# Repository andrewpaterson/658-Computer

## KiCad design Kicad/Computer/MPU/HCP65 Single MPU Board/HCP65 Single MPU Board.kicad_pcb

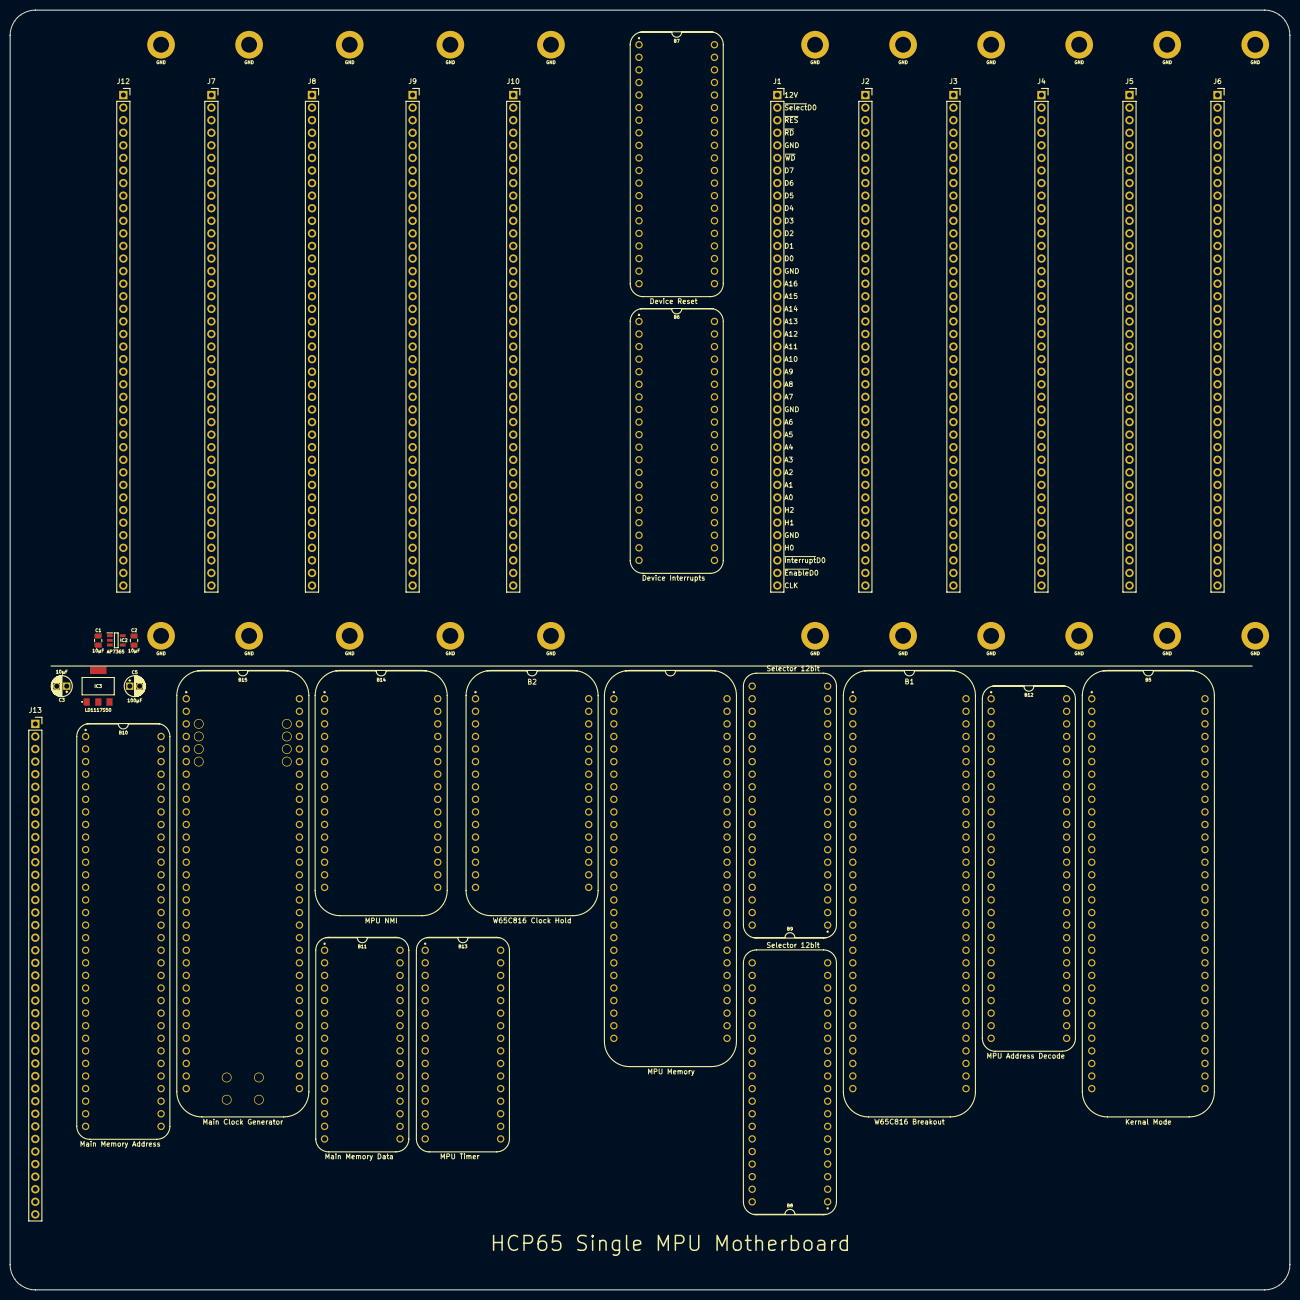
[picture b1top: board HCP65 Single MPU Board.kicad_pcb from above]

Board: 2 copper layers, 258.4 x 258.4 mm, 54 parts (0 on the bottom side), 186 nets, no tracks yet.

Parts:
B1: W65C816 Breakout; HCP65_W65C816_Breakout
B2: W65C816 Clock Hold; HCP65_W65C816_Clock_Hold
B4: MPU Memory; HCP65_MPU_Memory
B5: Kernal Mode; HCP65_Kernal_Mode
B6: Device Interrupts; HCP65_Device_Interrupts
B7: Device Reset; HCP65_Device_Reset
B8, B9: Selector 12bit; HCP65_Selector_12bit
B10: Main Memory Address; HCP65_Main_Memory_Address
B11: Main Memory Data; HCP65_Main_Memory_Data
B12: MPU Address Decode; HCP65_MPU_Address_Decode
B13: MPU Timer; HCP65_MPU_Timer
B14: MPU NMI; HCP65_MPU_NMI
B15: Main Clock Generator; HCP65_Clock_Generator
C1, C2: 10µF; C_0805
C3: 10μF; CP_Radial_D4.0mm_P2.00mm
C5: 100μF; CP_Radial_D4.0mm_P2.00mm
H3, H4, H5, H6, H7, H8, H9, H10, H11, H12, H13, H14, H15, H16, H17, H18, H19, H20, H21, H22, H23, H24: MountingHole_Pad; HCP65_MountingHole_M3_
IC2: AP7365-33WG-7; SOT95P285X130-5N
IC3: LD1117S50C; LD1117S33C
J1, J2, J3, J4, J5, J6, J7, J8, J9, J10, J12, J13: Conn_01x40_Socket; PinSocket_1x40_P2.54mm_Vertical

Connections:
/3.3V: B1.20 (BE), B1.21 (RDY), B1.44 (~ABORT), B2.4 (~Hold_High), B2.16 (~Hold_Low), B7.24 (~Enables_8..15), B9.16 (B10), B9.17 (B9), B9.21 (B6), B9.22 (B5), B9.23 (B4), B14.29 (~Set_Break_1), B14.30 (~Set_Break_2), B14.31 (~Set_Break_3), C2.1, IC2.5 (3.3VOut)
/5V: B1.3 (5V), B1.35 (5V), B2.1 (5V), B2.17 (5V), B4.3 (5V), B4.31 (5V), B5.3 (5V), B5.35 (5V), B6.20 (5V), B7.3 (5V), B7.23 (5V), B8.20 (5V), B9.20 (5V), B10.3 (5V), B10.35 (5V), B11.1 (5V), B11.17 (5V), B12.3 (5V), B12.31 (5V), B13.1 (5V), B13.17 (5V), B14.1 (5V), B14.17 (5V), B15.3 (5V), B15.35 (5V), C1.1, C5.1, IC2.1 (6VIn), IC2.3 (EN), IC3.2 (5.0VOut)
/12V: C3.1, IC3.3 (15VIn), J1.1, J2.1, J3.1, J4.1, J5.1, J6.1, J7.1, J8.1, J9.1, J10.1, J12.1, J13.1
/A0: B1.2 (A0), B8.14 (A0), B10.32 (A0), B12.52 (A0), J1.33, J2.33, J3.33, J4.33, J5.33, J6.33, J7.33, J8.33, J9.33, J10.33, J12.33
/A1: B1.4 (A1), B8.13 (A1), B10.31 (A1), B12.51 (A1), J1.32, J2.32, J3.32, J4.32, J5.32, J6.32, J7.32, J8.32, J9.32, J10.32, J12.32
/A2: B1.5 (A2), B8.12 (A2), B10.29 (A2), B12.50 (A2), J1.31, J2.31, J3.31, J4.31, J5.31, J6.31, J7.31, J8.31, J9.31, J10.31, J12.31
/A3: B1.6 (A3), B8.11 (A3), B10.28 (A3), B12.49 (A3), J1.30, J2.30, J3.30, J4.30, J5.30, J6.30, J7.30, J8.30, J9.30, J10.30, J12.30
/A4: B1.7 (A4), B8.10 (A4), B10.27 (A4), J1.29, J2.29, J3.29, J4.29, J5.29, J6.29, J7.29, J8.29, J9.29, J10.29, J12.29
/A5: B1.8 (A5), B8.9 (A5), B10.26 (A5), J1.28, J2.28, J3.28, J4.28, J5.28, J6.28, J7.28, J8.28, J9.28, J10.28, J12.28
/A6: B1.9 (A6), B8.8 (A6), B10.25 (A6), J1.27, J2.27, J3.27, J4.27, J5.27, J6.27, J7.27, J8.27, J9.27, J10.27, J12.27
/A7: B1.11 (A7), B8.7 (A7), B10.24 (A7), J1.25, J2.25, J3.25, J4.25, J5.25, J6.25, J7.25, J8.25, J9.25, J10.25, J12.25
/A8: B1.12 (A8), B8.6 (A8), B10.22 (A8), J1.24, J2.24, J3.24, J4.24, J5.24, J6.24, J7.24, J8.24, J9.24, J10.24, J12.24
/A9: B1.13 (A9), B8.5 (A9), B10.21 (A9), J1.23, J2.23, J3.23, J4.23, J5.23, J6.23, J7.23, J8.23, J9.23, J10.23, J12.23
/A10: B1.14 (A10), B8.4 (A10), B10.20 (A10), J1.22, J2.22, J3.22, J4.22, J5.22, J6.22, J7.22, J8.22, J9.22, J10.22, J12.22
/A11: B1.15 (A11), B8.3 (A11), B10.19 (A11), J1.21, J2.21, J3.21, J4.21, J5.21, J6.21, J7.21, J8.21, J9.21, J10.21, J12.21
/A12: B1.16 (A12), B9.14 (A0), B10.18 (A12), J1.20, J2.20, J3.20, J4.20, J5.20, J6.20, J7.20, J8.20, J9.20, J10.20, J12.20
/A13: B1.17 (A13), B9.13 (A1), B10.17 (A13), J1.19, J2.19, J3.19, J4.19, J5.19, J6.19, J7.19, J8.19, J9.19, J10.19, J12.19
/A14: B1.18 (A14), B9.12 (A2), B10.16 (A14), J1.18, J2.18, J3.18, J4.18, J5.18, J6.18, J7.18, J8.18, J9.18, J10.18, J12.18
/A15: B1.19 (A15), B9.11 (A3), B10.15 (A15), B12.47 (A15), J1.17, J2.17, J3.17, J4.17, J5.17, J6.17, J7.17, J8.17, J9.17, J10.17, J12.17
/A16: B5.53 (A_{OUT}16), B10.14 (A16), J1.16, J2.16, J3.16, J4.16, J5.16, J6.16, J7.16, J8.16, J9.16, J10.16, J12.16
/A17: B5.52 (A_{OUT}17), B10.13 (A17)
/A18: B5.51 (A_{OUT}18), B10.12 (A18)
/A19: B5.50 (A_{OUT}19), B10.11 (A19)
/A20: B5.49 (A_{OUT}20), B10.9 (A20)
/A21: B5.48 (A_{OUT}21), B10.8 (A21)
/A22: B5.47 (A_{OUT}22), B10.7 (A22)
/A23: B5.46 (A_{OUT}23), B10.6 (A23)
/BA0: B1.38 (BA0), B5.15 (BA_{IN}0), B8.27 (B0), B9.10 (A4), B12.46 (A16)
/BA1: B1.37 (BA1), B5.16 (BA_{IN}1), B8.26 (B1), B9.9 (A5), B12.45 (A17)
/BA2: B1.36 (BA2), B5.17 (BA_{IN}2), B8.25 (B2), B9.8 (A6), B12.44 (A18)
/BA3: B1.34 (BA3), B5.18 (BA_{IN}3), B8.24 (B3), B12.43 (A19)
/BA4: B1.29 (BA4), B5.19 (BA_{IN}4), B8.23 (B4), B12.42 (A20)
/BA5: B1.28 (BA5), B5.20 (BA_{IN}5), B8.22 (B5), B12.41 (A21)
/BA6: B1.27 (BA6), B5.21 (BA_{IN}6), B8.21 (B6), B12.40 (A22)
/BA7: B1.26 (BA7), B5.22 (BA_{IN}7), B8.19 (B7), B12.39 (A23)
/CLK: B2.3 (CLK), B7.21 (~CLK), B13.6 (CLK), J1.40, J2.40, J3.40, J4.40, J5.40, J6.40, J7.40, J8.40, J9.40, J10.40, J12.40
/CLK_{IN}: B2.6 (~CLK_{IN}), B15.11 (CLK_{0})
/D0: B1.53 (D0), B4.46 (D0), B5.33 (D0), B6.11 (D0), B7.11 (D0), B11.15 (D0), B13.8 (D0), B14.8 (D0), J1.14, J2.14, J3.14, J4.14, J5.14, J6.14, J7.14, J8.14, J9.14, J10.14, J12.14
/D1: B1.52 (D1), B4.45 (D1), B5.34 (D1), B6.12 (D1), B7.12 (D1), B11.14 (D1), B13.9 (D1), B14.9 (D1), J1.13, J2.13, J3.13, J4.13, J5.13, J6.13, J7.13, J8.13, J9.13, J10.13, J12.13
/D2: B1.51 (D2), B4.44 (D2), B5.36 (D2), B6.13 (D2), B7.13 (D2), B11.13 (D2), B13.10 (D2), B14.10 (D2), J1.12, J2.12, J3.12, J4.12, J5.12, J6.12, J7.12, J8.12, J9.12, J10.12, J12.12
/D3: B1.50 (D3), B4.43 (D3), B5.37 (D3), B6.14 (D3), B7.15 (D3), B11.11 (D3), B13.11 (D3), B14.11 (D3), J1.11, J2.11, J3.11, J4.11, J5.11, J6.11, J7.11, J8.11, J9.11, J10.11, J12.11
/D4: B1.49 (D4), B4.42 (D4), B5.38 (D4), B6.15 (D4), B7.16 (D4), B11.10 (D4), B13.13 (D4), B14.13 (D4), J1.10, J2.10, J3.10, J4.10, J5.10, J6.10, J7.10, J8.10, J9.10, J10.10, J12.10
/D5: B1.48 (D5), B4.41 (D5), B5.39 (D5), B6.16 (D5), B7.17 (D5), B11.9 (D5), B13.14 (D5), B14.14 (D5), J1.9, J2.9, J3.9, J4.9, J5.9, J6.9, J7.9, J8.9, J9.9, J10.9, J12.9
/D6: B1.47 (D6), B4.40 (D6), B5.40 (D6), B6.17 (D6), B7.18 (D6), B11.8 (D6), B13.15 (D6), B14.15 (D6), J1.8, J2.8, J3.8, J4.8, J5.8, J6.8, J7.8, J8.8, J9.8, J10.8, J12.8
/D7: B1.46 (D7), B4.39 (D7), B5.41 (D7), B6.18 (D7), B7.19 (D7), B11.7 (D7), B13.16 (D7), B14.16 (D7), J1.7, J2.7, J3.7, J4.7, J5.7, J6.7, J7.7, J8.7, J9.7, J10.7, J12.7
/Enter Interrupt: B5.62 (Enter_Interrupt), B14.27 (Set_Disable_NMI)
/GND: B1.10 (GND), B1.23 (GND), B1.42 (GND), B1.55 (GND), B2.5 (GND), B2.12 (GND), B2.13 (Hold_Count_{3}D), B2.21 (GND), B2.28 (GND), B4.9 (GND), B4.20 (GND), B4.37 (GND), B4.48 (GND), B5.10 (GND), B5.23 (GND), B5.42 (GND), B5.55 (GND), B6.21 (GND), B6.40 (GND), B7.7 (GND), B7.14 (GND), B7.27 (GND), B7.34 (GND), B8.1 (~E), B8.40 (GND), B9.1 (~E), B9.7 (A7), B9.15 (B11), B9.18 (B8), B9.19 (B7), B9.40 (GND), B10.10 (GND), B10.23 (GND), B10.30 (S), B10.42 (GND), B10.55 (GND), B11.5 (GND), B11.12 (GND), B11.21 (GND), B11.28 (GND), B12.9 (GND), B12.20 (GND), B12.37 (GND), B12.48 (GND), B13.5 (GND), B13.12 (GND), B13.21 (GND), B13.28 (GND), B14.5 (GND), B14.6 (MPU1), B14.7 (MPU0), B14.12 (GND), B14.21 (GND), B14.28 (GND), B15.6 (GND), B15.10 (GND), B15.23 (GND), B15.42 (GND), B15.55 (GND), C1.2, C2.2, C3.2, C5.2, H3.1 (GND), H4.1 (GND), H5.1 (GND), H6.1 (GND), H7.1 (GND), H8.1 (GND), H9.1 (GND), H10.1 (GND), H11.1 (GND), H12.1 (GND), H13.1 (GND), H14.1 (GND), H15.1 (GND), H16.1 (GND), H17.1 (GND), H18.1 (GND), H19.1 (GND), H20.1 (GND), H21.1 (GND), H22.1 (GND), H23.1 (GND), H24.1 (GND), IC2.2 (GND), IC3.1 (GND), J1.5, J1.15, J1.26, J1.36, J2.5, J2.15, J2.26, J2.36, J3.5, J3.15, J3.26, J3.36, J4.5, J4.15, J4.26, J4.36, J5.5, J5.15, J5.26, J5.36, J6.5, J6.15, J6.26, J6.36, J7.5, J7.15, J7.26, J7.36, J8.5, J8.15, J8.26, J8.36, J9.5, J9.15, J9.26, J9.36, J10.5, J10.15, J10.26, J10.36, J12.5, J12.15, J12.26, J12.36, J13.5, J13.15, J13.26, J13.36
/H0: B2.9 (Hold_Count_{0}D), B4.52 (H2), J1.37, J2.37, J3.37, J4.37, J5.37, J6.37, J7.37, J8.37, J9.37, J10.37, J12.37
/H1: B2.10 (Hold_Count_{1}D), B4.51 (H1), J1.35, J2.35, J3.35, J4.35, J5.35, J6.35, J7.35, J8.35, J9.35, J10.35, J12.35
/H2: B2.11 (Hold_Count_{2}D), B4.50 (H0), J1.34, J2.34, J3.34, J4.34, J5.34, J6.34, J7.34, J8.34, J9.34, J10.34, J12.34
/Kernal Mode: B5.56 (Kernal_Mode), B12.38 (Kernal_Mode)
/MA0: B10.33 (MA0), J13.31
/MA1: B10.34 (MA1), J13.30
/MA2: B10.36 (MA2), J13.29
/MA3: B10.37 (MA3), J13.28
/MA4: B10.38 (MA4), J13.27
/MA5: B10.39 (MA5), J13.25
/MA6: B10.40 (MA6), J13.24
/MA7: B10.41 (MA7), J13.23
/MA8: B10.43 (MA8), J13.22
/MA9: B10.44 (MA9), J13.21
/MA10: B10.45 (MA10), J13.20
/MA11: B10.46 (MA11), J13.19
/MA12: B10.47 (MA12), J13.18
/MA13: B10.48 (MA13), J13.17
/MA14: B10.49 (MA14), J13.16
/MA15: B10.50 (MA15), J13.14
/MA16: B10.51 (MA16), J13.13
/MA17: B10.52 (MA17), J13.12
/MA18: B10.53 (MA18), J13.11
/MA19: B10.54 (MA19), J13.10
/MA20: B10.56 (MA20), J13.9
/MA21: B10.57 (MA21), J13.8
/MA22: B10.58 (MA22), J13.7
/MA23: B10.59 (MA23), J13.6
/MD0: B11.18 (MD0), J13.40
/MD1: B11.19 (MD1), J13.39
/MD2: B11.20 (MD2), J13.38
/MD3: B11.22 (MD3), J13.37
/MD4: B11.23 (MD4), J13.35
/MD5: B11.24 (MD5), J13.34
/MD6: B11.25 (MD6), J13.33
/MD7: B11.26 (MD7), J13.32
/M~RD: B10.61 (M~RD), J13.3
/M~WD: B10.60 (M~WD), J13.4
/Native Latch: B1.57 (Native_Latch), B5.2 (Native_Latch), B12.30 (Native_Latch), B13.18 (~Hold)
/Opcode Valid: B1.1 (Opcode_Valid), B5.64 (Opcode_Valid)
/PHI2: B1.30 (Bank_Latch), B1.39 (PHI2), B1.45 (DE), B1.58 (~Trans_Output), B2.8 (PHI2)
/RTI: B5.63 (RTI), B14.26 (Set_Enable_NMI)
/SA0: B4.6 (A0), B8.28 (Q0)
/SA1: B4.7 (A1), B8.29 (Q1)
/SA2: B4.8 (A2), B8.30 (Q2)
/SA3: B4.10 (A3), B8.31 (Q3)
/SA4: B4.11 (A4), B8.32 (Q4)
/SA5: B4.12 (A5), B8.33 (Q5)
/SA6: B4.13 (A6), B8.34 (Q6)
/SA7: B4.14 (A7), B8.35 (Q7)
/SA8: B4.15 (A8), B8.36 (Q8)
/SA9: B4.16 (A9), B8.37 (Q9)
/SA10: B4.17 (A10), B8.38 (Q10)
/SA11: B4.19 (A11), B8.39 (Q11)
/SA12: B4.21 (A12), B9.28 (Q0)
/SA13: B4.22 (A13), B9.29 (Q1)
/SA14: B4.23 (A14), B9.30 (Q2)
/SA15: B4.24 (A15), B9.31 (Q3)
/SA16: B4.25 (A16), B9.32 (Q4)
/SA17: B4.26 (A17), B9.33 (Q5)
/SA18: B4.33 (A18), B9.34 (Q6)
/S~RAM_{CS}: B4.47 (~RAM), B9.39 (Q11)
/S~RD: B4.27 (~WD), B9.36 (Q8)
/S~ROM_{CS}: B4.49 (~ROM), B9.38 (Q10)
/S~WD: B4.28 (~RD), B9.37 (Q9)
/UP0: B5.32 (UP0), B8.18 (B8)
/UP1: B5.31 (UP1), B8.17 (B9)
/UP2: B5.30 (UP2), B8.16 (B10)
/UP3: B5.29 (UP3), B8.15 (B11)
/UP4: B5.28 (UP4), B9.27 (B0)
/UP5: B5.27 (UP5), B9.26 (B1)
/UP6: B5.26 (UP6), B9.25 (B2)
/UP7: B5.25 (UP7), B9.24 (B3)
/~CLK: B2.7 (~CLK), B8.2 (S), B9.2 (S)
/~Device Enable_{ 1..7}: B6.8 (~Device_Enable_{_1..7}), B7.25 (~Enables_1..7), B12.11 (~Special__{CS3})
/~Device Enable_{ 16..19}: B6.10 (~Device_Enable_{_16..19}), B7.22 (~Enables_16..19), B12.8 (~Special__{CS5})
/~Device Interrupt_{ 1..7}: B6.6 (~Device_Interrupt_{_1..7}), B12.14 (~Special__{CS0})
/~Device Interrupt_{ 16..19}: B6.7 (~Device_Interrupt_{_16..19}), B12.12 (~Special__{CS2})
/~Enable_{Device}1: B6.31 (~Enable_{Device}1), J1.39
/~Enable_{Device}2: B6.30 (~Enable_{Device}2), J2.39
/~Enable_{Device}3: B6.29 (~Enable_{Device}3), J4.39
/~Enable_{Device}4: B6.28 (~Enable_{Device}4), J3.39
/~Enable_{Device}5: B6.27 (~Enable_{Device}5), J6.39
/~Enable_{Device}6: B6.26 (~Enable_{Device}6), J5.39
/~Enable_{Device}7: B6.25 (~Enable_{Device}7), J12.39
/~Enable_{Device}16: B6.24 (~Enable_{Device}16), J10.39
/~Enable_{Device}17: B6.23 (~Enable_{Device}17), J9.39
/~Enable_{Device}18: B6.22 (~Enable_{Device}18), J8.39
/~Enable_{Device}19: B6.19 (~Enable_{Device}19), J7.39
/~IRQ: B1.43 (~IRQ), B6.39 (~INT)
/~Interrupt Depth: B5.59 (~Interrupt_Depth), B12.4 (~Special__{CS9})
/~Interrupt_{Device}1: B6.4 (~Interrupt_{Device}1), J1.38
/~Interrupt_{Device}2: B6.3 (~Interrupt_{Device}2), J2.38
/~Interrupt_{Device}3: B6.2 (~Interrupt_{Device}3), J4.38
/~Interrupt_{Device}4: B6.1 (~Interrupt_{Device}4), J3.38
/~Interrupt_{Device}5: B6.38 (~Interrupt_{Device}5), J6.38
/~Interrupt_{Device}6: B6.37 (~Interrupt_{Device}6), J5.38
/~Interrupt_{Device}7: B6.36 (~Interrupt_{Device}7), J12.38
/~Interrupt_{Device}16: B6.35 (~Interrupt_{Device}16), J10.38
/~Interrupt_{Device}17: B6.34 (~Interrupt_{Device}17), J9.38
/~Interrupt_{Device}18: B6.33 (~Interrupt_{Device}18), J8.38
/~Interrupt_{Device}19: B6.32 (~Interrupt_{Device}19), J7.38
/~Main Access Slot: B10.1 (~Main_Access_Slot), B11.2 (~Main_Access_Slot), B15.12 (~Main_Access_{0})
/~Main: B4.54 (~Main), B10.2 (~Main), B11.3 (~Main), B12.36 (~Other), J13.2
/~NMI Speed Select: B12.7 (~Special__{CS6}), B13.7 (~NMI_Rate_Select)
/~NMI State: B12.6 (~Special__{CS7}), B14.23 (~NMI_State)
/~NMI: B1.41 (~NMI), B14.32 (~NMI)
/~PHI2: B2.26 (~PHI2), B5.5 (Latch_Bank_Remap)
/~RAM_{CS}: B9.3 (A11), B12.32 (~RAM_{CS})
/~RD: B1.61 (~RD), B5.58 (~RD), B6.9 (~RD), B9.6 (A8), B10.4 (~RD), B11.4 (~RD), B13.3 (~RD), B14.3 (~RD), J1.4, J2.4, J3.4, J4.4, J5.4, J6.4, J7.4, J8.4, J9.4, J10.4, J12.4
/~ROM_{CS}: B9.4 (A10), B12.33 (~ROM_{CS})
/~Reset: B1.40 (~Reset), B2.32 (~Reset), B7.40 (~Reset), B12.26 (~Reset), B13.2 (~Reset), B14.2 (~Reset), B15.9 (~Reset)
/~Reset_{Device}1: B7.1 (~Reset_1), J1.3
/~Reset_{Device}2: B7.2 (~Reset_2), J2.3
/~Reset_{Device}3: B7.4 (~Reset_3), J4.3
/~Reset_{Device}4: B7.36 (~Reset_4), J3.3
/~Reset_{Device}5: B7.37 (~Reset_5), J6.3
/~Reset_{Device}6: B7.38 (~Reset_6), J5.3
/~Reset_{Device}7: B7.39 (~Reset_7), J12.3
/~Reset_{Device}16: B7.30 (~Reset_16), J10.3
/~Reset_{Device}17: B7.29 (~Reset_17), J9.3
/~Reset_{Device}18: B7.28 (~Reset_18), J8.3
/~Reset_{Device}19: B7.26 (~Reset_19), J7.3
/~Select_{Device}1: B12.27 (~Device__{CS1}), J1.2
/~Select_{Device}2: B12.25 (~Device__{CS2}), J2.2
/~Select_{Device}3: B12.24 (~Device__{CS3}), J4.2
/~Select_{Device}4: B12.23 (~Device__{CS4}), J3.2
/~Select_{Device}5: B12.22 (~Device__{CS5}), J6.2
/~Select_{Device}6: B12.21 (~Device__{CS6}), J5.2
/~Select_{Device}7: B12.19 (~Device__{CS7}), J12.2
/~Select_{Device}16: B12.18 (~Device__{CS16}), J10.2
/~Select_{Device}17: B12.17 (~Device__{CS17}), J9.2
/~Select_{Device}18: B12.16 (~Device__{CS18}), J8.2
/~Select_{Device}19: B12.15 (~Device__{CS19}), J7.2
/~Special: B4.53 (~Special), B12.28 (~Special)
/~Timer: B13.26 (~Set_Timer), B14.25 (~Set_Timer)
/~User Program: B5.60 (~User_Program), B12.5 (~Special__{CS8})
/~VP: B1.59 (VDA), B5.1 (~VP)
/~WD: B1.60 (~WD), B5.54 (~WD), B7.20 (~WD), B9.5 (A9), B10.5 (~WD), B11.6 (~WD), B13.4 (~WD), B14.4 (~WD), J1.6, J2.6, J3.6, J4.6, J5.6, J6.6, J7.6, J8.6, J9.6, J10.6, J12.6

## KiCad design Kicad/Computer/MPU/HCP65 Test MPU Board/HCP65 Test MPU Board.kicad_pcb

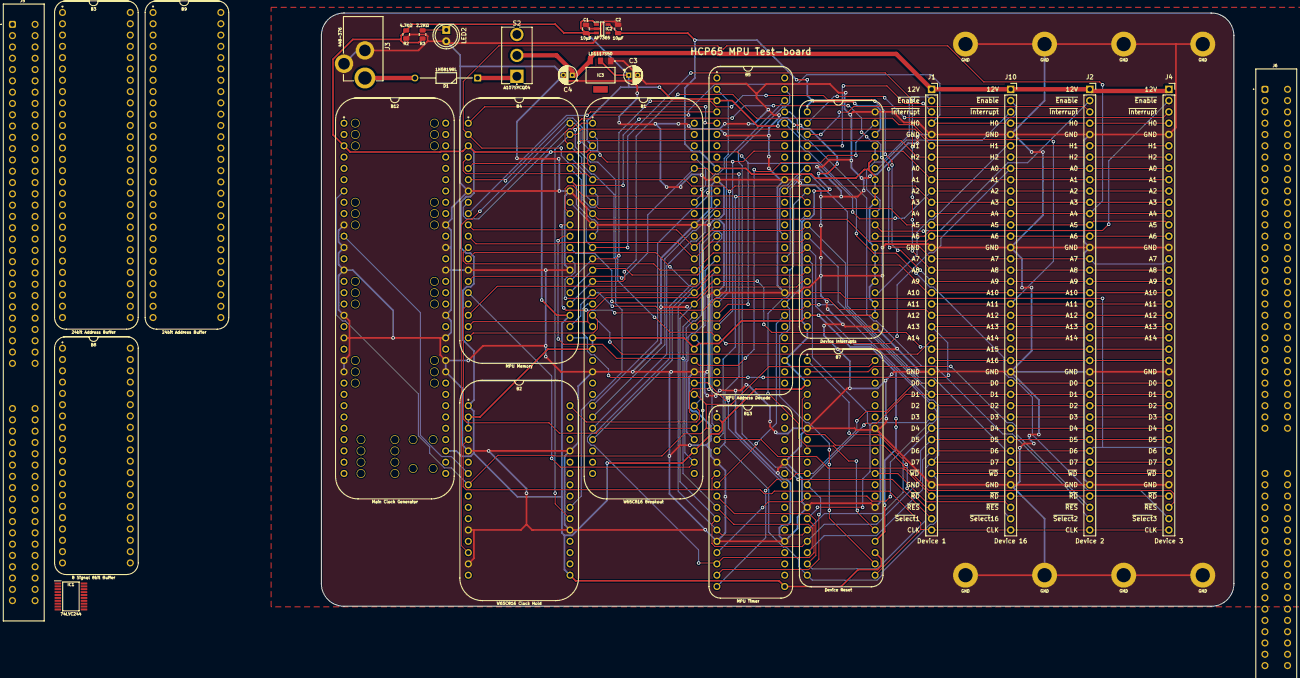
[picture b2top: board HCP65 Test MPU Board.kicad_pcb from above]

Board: 2 copper layers, 205.1 x 133.3 mm, 38 parts (0 on the bottom side), 78 nets.

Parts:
B1: W65C816 Breakout; HCP65_W65C816_Breakout
B2: W65C816 Clock Hold; HCP65_W65C816_Clock_Hold
B3, B9: 24bit Address Buffer; HCP65_Address_Buffer
B4: MPU Memory; HCP65_MPU_Memory
B5: MPU Address Decode; HCP65_MPU_Address_Decode
B6: Device Interrupts; HCP65_Device_Interrupts
B7: Device Reset; HCP65_Device_Reset
B8: 8 Signal 8bit Data Buffer; HCP65_Data_and_Signal_Buffer
B12: Main Clock Generator; HCP65_Clock_Generator
B13: MPU Timer; HCP65_MPU_Timer
C1, C2: 10µF; C_0805
C3, C4: C_Polarized; CP_Radial_D4.0mm_P2.00mm
D1: 1N5819RL; DIOAD1414W86L464D238
H8, H9, H12, H16, H17, H19, H21, H24: MountingHole_Pad; HCP65_MountingHole_M3_
IC1: 74LVC244APW,118; SOP65P640X110-20N
IC2: AP7365-33WG-7; SOT95P285X130-5N
IC3: LD1117S50C; LD1117S33C
J1, J2, J4, J10: Conn_01x40_Socket; PinSocket_1x40_P2.54mm_Vertical
J3: 448-376; 448376
J5, J6: 395-098-520-350; 395098520350
LED2: LED; LED_D5.0mm
R2: 4.7KΩ; R_0805
R3: 2.2KΩ; R_0805
S2: A107SYCQ04

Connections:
/3.3V: B1.20 (BE), B1.21 (RDY), B1.44 (~ABORT), B2.2 (~Hold_Low), B2.3 (~Hold_High), B5.9 (Kernal_Mode), B6.1 (~Interrupt_{Device}4), B6.19 (~Enable_{Device}19), B6.22 (~Enable_{Device}18), B6.23 (~Enable_{Device}17), B6.25 (~Enable_{Device}7), B6.26 (~Enable_{Device}6), B6.27 (~Enable_{Device}5), B6.28 (~Enable_{Device}4), B6.32 (~Interrupt_{Device}19), B6.33 (~Interrupt_{Device}18), B6.34 (~Interrupt_{Device}17), B6.36 (~Interrupt_{Device}7), B6.37 (~Interrupt_{Device}6), B6.38 (~Interrupt_{Device}5), C2.1, IC1.2 (1A0), IC1.19 (~2OE), IC1.20 (3V), IC2.5 (VOUT)
/5V: B1.3 (5V), B1.35 (5V), B2.1 (5V), B2.17 (5V), B4.3 (5V), B4.23 (5V), B5.3 (5V), B5.31 (5V), B6.20 (5V), B7.3 (5V), B7.23 (5V), B8.3 (5V), B8.23 (5V), B9.3 (5V), B9.31 (5V), B12.3 (5V), B12.35 (5V), B13.1 (5V), B13.17 (5V), C1.1, C3.1, IC2.1 (VIN), IC2.3 (EN), IC3.2 (5.0VOut), R2.1, R3.2
/12V: C4.1, IC3.3 (15VIn), J1.1, J2.1, J4.1, J10.1, S2.2 (CM)
/12V Forward: D1.1, S2.1
/12V Socket: D1.2, J3.A1 (VCC)
/A0: B1.1 (A0), B3.28 (A0_{IN}), B4.8 (A0), B5.24 (A0), B9.28 (A0_{IN}), J1.8, J2.8, J4.8, J10.8
/A1: B1.2 (A1), B3.27 (A1_{IN}), B4.6 (A1), B5.23 (A1), B9.27 (A1_{IN}), J1.9, J2.9, J4.9, J10.9
/A2: B1.5 (A2), B3.26 (A2_{IN}), B4.5 (A2), B5.22 (A2), B9.26 (A2_{IN}), J1.10, J2.10, J4.10, J10.10
/A3: B1.6 (A3), B3.25 (A3_{IN}), B4.4 (A3), B5.21 (A3), B9.25 (A3_{IN}), J1.11, J2.11, J4.11, J10.11
/A4: B1.7 (A4), B3.24 (A4_{IN}), B4.2 (A4), B9.24 (A4_{IN}), J1.12, J2.12, J4.12, J10.12
/A5: B1.8 (A5), B3.23 (A5_{IN}), B4.37 (A5), B9.23 (A5_{IN}), J1.13, J2.13, J4.13, J10.13
/A6: B1.9 (A6), B3.22 (A7_{IN}), B4.36 (A6), B9.22 (A7_{IN}), J1.14, J2.14, J4.14, J10.14
/A7: B1.11 (A7), B3.21 (A7_{IN}), B4.35 (A7), B9.21 (A7_{IN}), J1.16, J2.16, J4.16, J10.16
/A8: B1.12 (A8), B3.19 (A8_{IN}), B4.33 (A8), B9.19 (A8_{IN}), J1.17, J2.17, J4.17, J10.17
/A9: B1.13 (A9), B3.18 (A9_{IN}), B4.26 (A9), B9.18 (A9_{IN}), J1.18, J2.18, J4.18, J10.18
/A10: B1.14 (A10), B3.17 (A10_{IN}), B4.25 (A10), B9.17 (A10_{IN}), J1.19, J2.19, J4.19, J10.19
/A11: B1.15 (A11), B3.16 (A11_{IN}), B4.24 (A11), B9.16 (A11_{IN}), J1.20, J2.20, J4.20, J10.20
/A12: B1.16 (A12), B3.15 (A12_{IN}), B4.22 (A12), B9.15 (A12_{IN}), J1.21, J2.21, J4.21, J10.21
/A13: B1.17 (A13), B3.14 (A13_{IN}), B4.21 (A13), B9.14 (A13_{IN}), J1.22, J2.22, J4.22, J10.22
/A14: B1.18 (A14), B3.12 (A14_{IN}), B4.20 (A14), B9.12 (A14_{IN}), J1.23, J2.23, J4.23, J10.23
/A15: B1.19 (A15), B3.11 (A15_{IN}), B4.19 (A15), B5.19 (A15), B9.11 (A15_{IN}), J10.24
/A16: B1.38 (BA0), B3.9 (A16_{IN}), B4.18 (A16), B5.18 (A16), B8.1 (S7_{IN}), J10.25
/A17: B1.37 (BA1), B3.8 (A17_{IN}), B4.17 (A17), B5.17 (A17)
/A18: B1.34 (BA3), B3.7 (A18_{IN}), B4.16 (A18), B5.16 (A18)
/A19: B1.36 (BA2), B3.6 (A19_{IN}), B5.15 (A19)
/A20: B1.29 (BA4), B3.5 (A20_{IN}), B5.14 (A20)
/A21: B1.28 (BA5), B3.4 (A21_{IN}), B5.13 (A21)
/A22: B1.27 (BA6), B3.2 (A22_{IN}), B5.12 (A22)
/A23: B1.26 (BA7), B3.1 (A23_{IN}), B5.11 (A23)
/CLK: B2.4 (CLK), B7.21 (~CLK), B8.8 (S2_{IN}), B13.6 (CLK), J1.40, J2.40, J4.40, J10.40
/CLK_{IN}: B2.7 (~CLK_{IN}), B12.11 (CLK_{0})
/D0: B1.53 (D0), B4.10 (D0), B6.11 (D0), B7.11 (D0), B8.20 (D0_{IN/OUT}), B13.16 (D0), J1.27, J2.27, J4.27, J10.27
/D1: B1.52 (D1), B4.11 (D1), B6.12 (D1), B7.12 (D1), B8.19 (D1_{IN/OUT}), B13.15 (D1), J1.28, J2.28, J4.28, J10.28
/D2: B1.51 (D2), B4.12 (D2), B6.13 (D2), B7.13 (D2), B8.18 (D2_{IN/OUT}), B13.13 (D3), J1.29, J2.29, J4.29, J10.29
/D3: B1.50 (D3), B4.13 (D3), B6.14 (D3), B7.15 (D3), B8.17 (D3_{IN/OUT}), B13.14 (D2), J1.30, J2.30, J4.30, J10.30
/D4: B1.49 (D4), B4.28 (D4), B6.15 (D4), B7.16 (D4), B8.16 (D4_{IN/OUT}), B13.11 (D4), J1.31, J2.31, J4.31, J10.31
/D5: B1.48 (D5), B4.29 (D5), B6.16 (D5), B7.17 (D5), B8.15 (D5_{IN/OUT}), B13.10 (D5), J1.32, J2.32, J4.32, J10.32
/D6: B1.47 (D6), B4.30 (D6), B6.17 (D6), B7.18 (D6), B8.13 (D6_{IN/OUT}), B13.9 (D6), J1.33, J2.33, J4.33, J10.33
/D7: B1.46 (D7), B4.31 (D7), B6.18 (D7), B7.19 (D7), B8.12 (D7_{IN/OUT}), B13.8 (D7), J1.34, J2.34, J4.34, J10.34
/GND: B1.10 (GND), B1.23 (GND), B1.42 (GND), B1.55 (GND), B2.5 (GND), B2.12 (GND), B2.15 (HC_Latch_{3}), B2.21 (GND), B2.28 (GND), B4.7 (GND), B4.14 (GND), B4.27 (GND), B4.34 (GND), B5.10 (GND), B5.20 (GND), B5.37 (GND), B5.47 (GND), B6.21 (GND), B6.40 (GND), B7.7 (GND), B7.14 (GND), B7.27 (GND), B7.34 (GND), B8.7 (GND), B8.14 (GND), B8.27 (GND), B8.34 (GND), B9.1 (A23_{IN}), B9.2 (A22_{IN}), B9.4 (A21_{IN}), B9.5 (A20_{IN}), B9.6 (A19_{IN}), B9.7 (A18_{IN}), B9.8 (A17_{IN}), B9.10 (GND), B9.20 (GND), B9.37 (GND), B9.47 (GND), B12.10 (GND), B12.12 (GND), B12.14 (GND), B12.18 (GND), B12.20 (GND), B12.22 (GND), B12.23 (GND), B12.42 (GND), B12.43 (GND), B12.45 (GND), B12.47 (GND), B12.51 (GND), B12.53 (GND), B12.55 (GND), B13.5 (GND), B13.12 (GND), B13.21 (GND), B13.28 (GND), C1.2, C2.2, C3.2, C4.2, H8.1 (GND), H9.1 (GND), H12.1 (GND), H16.1 (GND), H17.1 (GND), H19.1 (GND), H21.1 (GND), H24.1 (GND), IC1.4 (1A1), IC1.6 (1A2), IC1.8 (1A3), IC1.10 (GND), IC1.11 (2A3), IC1.13 (2A2), IC1.15 (2A1), IC1.17 (2A0), IC2.2 (GND), IC3.1 (GND), J1.5, J1.15, J1.26, J1.36, J2.5, J2.15, J2.26, J2.36, J3.B1 (GND), J3.C1 (GND), J4.5, J4.15, J4.26, J4.36, J10.5, J10.15, J10.26, J10.36, LED2.2 (A), R2.2
/H0: B2.23 (HC_Latch_{0}), B4.38 (CH0_{OUT}), B8.37 (S4), IC1.18 (1Y0), J1.4, J2.4, J4.4, J10.4
/H1: B2.22 (HC_Latch_{1}), B4.39 (CH1_{OUT}), B8.38 (S5), IC1.16 (1Y1), J1.6, J2.6, J4.6, J10.6
/H2: B2.14 (HC_Latch_{2}), B4.40 (CH2_{OUT}), B8.39 (S6), IC1.14 (1Y2), J1.7, J2.7, J4.7, J10.7
/Native Latch: B1.57 (Native_Latch), B5.2 (Native_Latch)
/PHI2: B1.39 (PHI2), B1.45 (DE), B2.32 (PHI2)
/~CLK: B2.6 (~CLK), B8.6 (S3_{IN})
/~Device Enable_{ 1..7}: B5.39 (~Special__{CS3}), B6.8 (~Device_Enable_{_1..7}), B7.25 (~Enables_1..7)
/~Device Enable_{ 8..15}: B5.38 (~Special__{CS4}), B7.24 (~Enables_8..15)
/~Device Enable_{ 16..19}: B5.36 (~Special__{CS5}), B6.10 (~Device_Enable_{_16..19}), B7.22 (~Enables_16..19)
/~Device Interrupt_{ 1..7}: B5.42 (~Special__{CS0}), B6.6 (~Device_Interrupt_{_1..7})
/~Device Interrupt_{ 16..19}: B5.40 (~Special__{CS2}), B6.7 (~Device_Interrupt_{_16..19})
/~Device: B5.1 (~Device), B8.11 (Device_~CS), B9.13 (Device_~CS)
/~Enable_{Device}1: B6.31 (~Enable_{Device}1), J1.2
/~Enable_{Device}2: B6.30 (~Enable_{Device}2), J2.2
/~Enable_{Device}3: B6.29 (~Enable_{Device}3), J4.2
/~Enable_{Device}16: B6.24 (~Enable_{Device}16), J10.2
/~IRQ: B1.43 (~IRQ), B6.39 (~INT)
/~Interrupt_{Device}1: B6.4 (~Interrupt_{Device}1), J1.3
/~Interrupt_{Device}2: B6.3 (~Interrupt_{Device}2), J2.3
/~Interrupt_{Device}3: B6.2 (~Interrupt_{Device}3), J4.3
/~Interrupt_{Device}16: B6.35 (~Interrupt_{Device}16), J10.3
/~RAM_{CS}: B4.9 (~RAM_{CS}), B5.4 (~RAM_{CS})
/~RD: B1.61 (~RD), B4.32 (~RD), B6.9 (~RD), B8.9 (~WD_{IN}), B8.31 (D_DIR), B13.3 (~RD), J1.37, J2.37, J4.37, J10.37
/~ROM_{CS}: B4.1 (~ROM_{CS}), B5.5 (~ROM_{CS})
/~Reset: B1.40 (~Reset), B2.8 (~Reset), B5.54 (~Reset), B7.40 (~Reset), B12.7 (~Reset_{OUT}), B13.2 (~Reset)
/~Reset_{Device}1: B7.1 (~Reset_1), J1.38
/~Reset_{Device}2: B7.2 (~Reset_2), J2.38
/~Reset_{Device}3: B7.4 (~Reset_3), J4.38
/~Reset_{Device}16: B7.30 (~Reset_16), J10.38
/~Select_{Device}1: B5.55 (~Device__{CS1}), J1.39
/~Select_{Device}2: B5.53 (~Device__{CS2}), J2.39
/~Select_{Device}3: B5.52 (~Device__{CS3}), J4.39
/~Select_{Device}16: B5.46 (~Device__{CS16}), J10.39
/~Special: B5.56 (~Special), IC1.1 (~1OE)
/~Timer Speed Select: B5.35 (~Special__{CS6}), B13.7 (~NMI_Rate_Select)
/~Timer: B1.41 (~NMI), B13.26 (~Set_Timer)
/~WD: B1.60 (~WD), B4.15 (~WD), B7.20 (~WD), B8.10 (~RD_{IN}), B13.4 (~WD), J1.35, J2.35, J4.35, J10.35
unnamed: LED2.1 (K), R3.1

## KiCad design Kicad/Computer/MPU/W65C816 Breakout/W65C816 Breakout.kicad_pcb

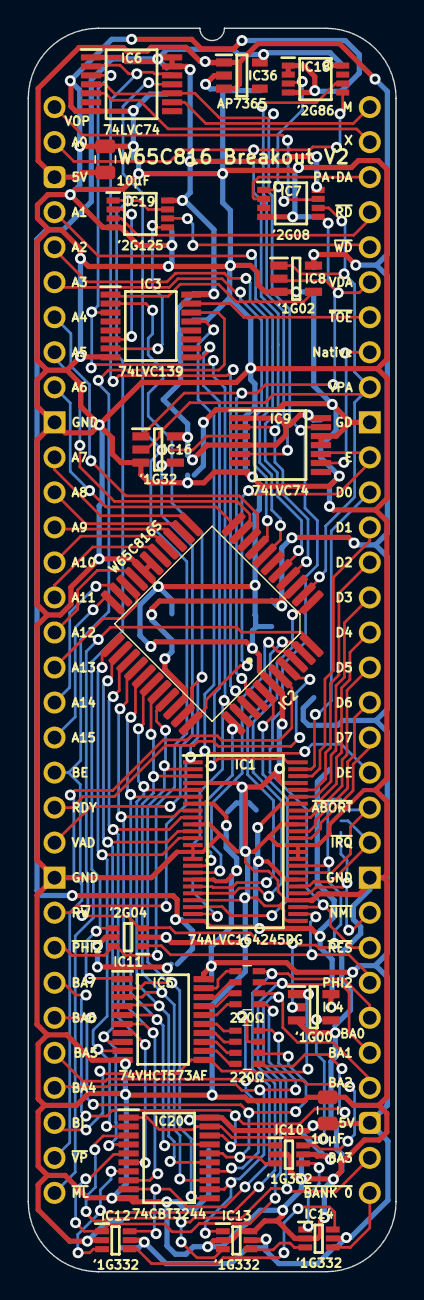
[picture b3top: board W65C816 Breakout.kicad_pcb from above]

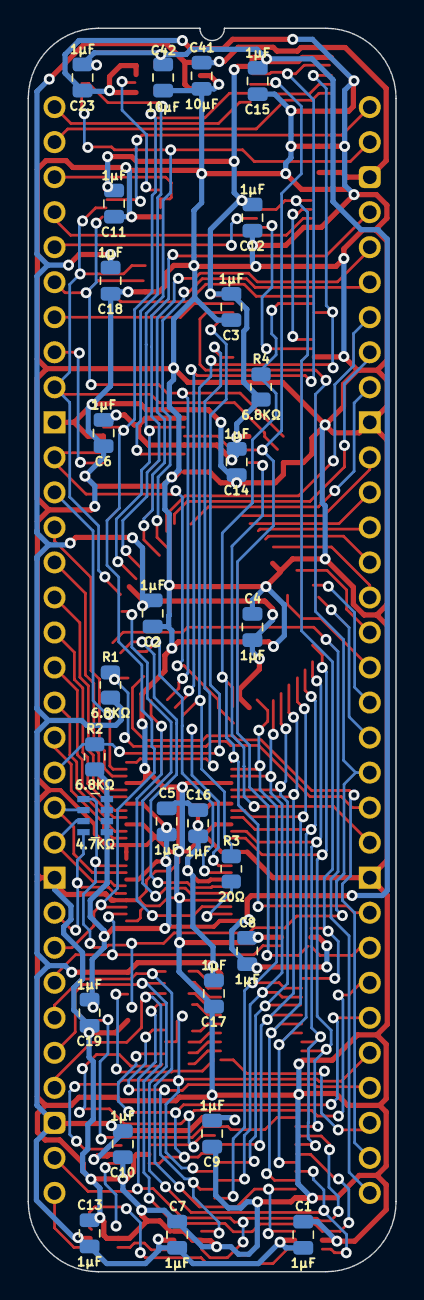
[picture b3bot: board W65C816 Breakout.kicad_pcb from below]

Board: 2 copper layers, 26.7 x 90.2 mm, 53 parts (29 on the bottom side), 96 nets.

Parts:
C1, C2, C3, C4, C5, C6, C7, C8, C9, C10, C11, C12, C13, C14, C15, C16, C17, C18, C19, C23: 1μF; C_0805
C20, C21, C41, C42: 10μF; C_0805
IC1: 74ALVC164245DGG,11; SOP50P810X120-48N
IC2: W65C816S6TQG-14; W65C816 PLCC 0.8mm 44 Pin
IC3: 74LVC139PW,118; SOP65P640X110-16N
IC4: 74LVC1G00GV,125; SOT95P275X110-5N
IC5: 74VHCT573AFT; SOP65P640X120-20N
IC6, IC9: 74LVC74APW,118; SOP65P640X110-14N
IC7: 74LVC2G08DP-Q100H; SOP65P400X110-8N
IC8: 74LVC1G02GV,125; SOT95P275X110-5N
IC10, IC12, IC13, IC14: SN74LVC1G332DCKRG4; SOT65P210X110-6N
IC11: 74LVC2G04GW-Q100H; SOP65P210X110-6N
IC16: 74LVC1G32GV,125; SOT95P275X110-5N
IC18: 74LVC2G86DP,125; SOP65P400X110-8N
IC19: 74LVC2G125DP,125; SOP65P400X110-8N
IC20: SN74CBT3244CPWR; SOP65P640X120-20N
IC36: AP7365-33WG-7; SOT95P285X130-5N
J1, J2: Pin_Header_01x32; PinHeader_1x32_P2.54mm_Vertical
J7: Conn_02x32_Counter_Clockwise; DIP-64_Board_W22.86mm
R1, R2, R4: 6.8KΩ; R_0805
R3: 20Ω; R_0805
RN1, RN2: CAY16-221J4LF; CAY16-F4
RN4: CAY16-472J4LF; CAY16-F4

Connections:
5V: C1.1, C2.1, C4.1, C7.1, C9.1, C10.1, C13.1, C16.1, C17.1, C18.1, C20.1, C21.1, C41.1, IC1.7 (5V), IC1.18 (5V), IC2.9 (VCC), IC2.37 (VCC), IC5.20 (5V), IC8.5 (3V), IC10.5 (3V), IC12.5 (3V), IC13.5 (3V), IC14.5 (3V), IC20.20 (5V), IC36.1 (6VIn), IC36.3 (EN), J7.3, J7.35, R1.1
/3.3V: C3.1, C5.1, C6.1, C8.1, C11.1, C12.1, C14.1, C15.1, C19.1, C23.1, C42.1, IC1.24 (2DIR), IC1.31 (3V), IC1.42 (3V), IC3.16 (3V), IC4.5 (3V), IC6.1 (~1RD), IC6.13 (~2RD), IC6.14 (3V), IC7.8 (3V), IC9.1 (~1RD), IC9.4 (~1SD), IC9.14 (3V), IC11.5 (3V), IC16.5 (3V), IC18.8 (VCC), IC19.8 (VCC), IC36.5 (3.3VOut), R2.1, R4.1, RN4.1 (R1), RN4.2 (R2), RN4.3 (R3), RN4.4 (R4)
/A0_{CHANGE}: IC7.1 (1A), IC18.3 (2Y)
/A0_{PREV}: IC9.5 (1Q), IC18.6 (2B)
/BA0+BA1+BA2: IC12.4 (Y), IC14.6 (C)
/BA3+BA4: IC13.4 (Y), IC14.3 (B)
/BA5+BA6+BA7: IC10.4 (Y), IC14.1 (A)
/BE_{5V}: IC1.16 (2B2), IC2.40 (BE)
/D0_{65}: IC1.2 (1B0), IC2.36 (D0), IC5.2 (D0), IC20.11 (2A1)
/D0_{VHC}: IC5.19 (Q0), RN2.1 (R1)
/D1_{65}: IC1.3 (1B1), IC2.35 (D1), IC5.3 (D1), IC20.13 (2A2)
/D1_{VHC}: IC5.18 (Q1), RN2.2 (R2)
/D2_{65}: IC1.5 (1B2), IC2.34 (D2), IC5.4 (D2), IC20.15 (2A3)
/D2_{VHC}: IC5.17 (Q2), RN2.3 (R3)
/D3_{65}: IC1.6 (1B3), IC2.33 (D3), IC5.5 (D3), IC20.17 (2A4)
/D3_{VHC}: IC5.16 (Q3), RN2.4 (R4)
/D4_{65}: IC1.8 (1B4), IC2.32 (D4), IC5.6 (D4), IC20.8 (1A4)
/D4_{VHC}: IC5.15 (Q4), RN1.1 (R1)
/D5_{65}: IC1.9 (1B5), IC2.31 (D5), IC5.7 (D5), IC20.6 (1A3)
/D5_{VHC}: IC5.14 (Q5), RN1.2 (R2)
/D6_{65}: IC1.11 (1B6), IC2.30 (D6), IC5.8 (D6), IC20.4 (1A2)
/D6_{VHC}: IC5.13 (Q6), RN1.3 (R3)
/D7_{65}: IC1.12 (1B7), IC2.29 (D7), IC5.9 (D7), IC20.2 (1A1)
/D7_{VHC}: IC5.12 (Q7), RN1.4 (R4)
/FET ~OE: IC4.4 (Y), IC20.1 (1~OE), IC20.19 (2~OE)
/MX: IC2.42 (MX), IC6.2 (1D), IC6.12 (2D)
/PHI2_{5V}: IC2.41 (PHI2), IC3.3 (1A1), IC6.3 (1CP), R3.2
/~ABORT_{5V}: IC1.17 (2B3), IC2.4 (~ABORT)
/~BE: IC5.1 (~OE), IC11.4 (2Y), IC19.1 (1~OE), IC19.7 (2~OE)
/~DE: IC1.48 (1~OE), IC3.9 (~2Y3)
/~IRQ_{5V}: IC1.19 (2B4), IC2.5 (~IRQ)
/~NMI_{5V}: IC1.20 (2B5), IC2.7 (~NMI)
/~RD_{PART}: IC3.7 (~1Y3), IC19.5 (2A)
/~RES_{5V}: IC1.22 (2B6), IC2.44 (~RES)
/~VPA+VDA: IC3.1 (~1E), IC8.4 (Y)
/~WD_{PART}: IC3.6 (~1Y2), IC19.2 (1A)
A0: IC2.10 (A0), IC9.2 (1D), IC18.5 (2A), J7.2
A1: IC2.11 (A1), J7.4
A2: IC2.13 (A2), J7.5
A3: IC2.14 (A3), J7.6
A4: IC2.15 (A4), J7.7
A5: IC2.16 (A5), J7.8
A6: IC2.17 (A6), J7.9
A7: IC2.18 (A7), J7.11
A8: IC2.19 (A8), J7.12
A9: IC2.20 (A9), J7.13
A10: IC2.21 (A10), J7.14
A11: IC2.22 (A11), J7.15
A12: IC2.25 (A12), J7.16
A13: IC2.26 (A13), J7.17
A14: IC2.27 (A14), J7.18
A15: IC2.28 (A15), J7.19
Address Valid: IC16.4 (Y), J7.22
BA0: IC12.6 (C), IC20.9 (2B1), J7.38, RN2.8 (R1)
BA1: IC12.3 (B), IC20.7 (2B2), J7.37, RN2.7 (R2)
BA2: IC12.1 (A), IC20.5 (2B3), J7.36, RN2.6 (R3)
BA3: IC13.3 (B), IC20.3 (2B4), J7.34, RN2.5 (R4)
BA4: IC13.1 (A), IC20.12 (1B4), J7.29, RN1.8 (R1)
BA5: IC10.6 (C), IC20.14 (1B3), J7.28, RN1.7 (R2)
BA6: IC10.3 (B), IC20.16 (1B2), J7.27, RN1.6 (R3)
BA7: IC10.1 (A), IC20.18 (1B1), J7.26, RN1.5 (R4)
BE: IC1.33 (2A2), IC3.14 (2A0), IC4.2 (A), IC11.3 (2A), J7.20, RN4.5 (R4)
Bank Latch: IC4.1 (B), IC5.11 (LE), J7.30
D0: IC1.47 (1A0), J7.53
D1: IC1.46 (1A1), J7.52
D2: IC1.44 (1A2), J7.51
D3: IC1.43 (1A3), J7.50
D4: IC1.41 (1A4), J7.49
D5: IC1.40 (1A5), J7.48
D6: IC1.38 (1A6), J7.47
D7: IC1.37 (1A7), J7.46
DE: IC3.13 (2A1), J7.45, R2.2
E: IC2.39 (E), IC9.10 (~2SD), J7.54
GND: C1.2, C2.2, C3.2, C4.2, C5.2, C6.2, C7.2, C8.2, C9.2, C10.2, C11.2, C12.2, C13.2, C14.2, C15.2, C16.2, C17.2, C18.2, C19.2, C20.2, C21.2, C23.2, C41.2, C42.2, IC1.4 (GND), IC1.10 (GND), IC1.13 (2B0), IC1.14 (2B1), IC1.15 (GND), IC1.21 (GND), IC1.25 (2~OE), IC1.28 (GND), IC1.34 (GND), IC1.35 (2A1), IC1.36 (2A0), IC1.39 (GND), IC1.45 (GND), IC2.1 (GND), IC2.23 (GND), IC2.24 (GND), IC3.8 (GND), IC4.3 (GND), IC5.10 (GND), IC6.7 (GND), IC7.4 (GND), IC8.3 (GND), IC9.7 (GND), IC9.11 (2CP), IC9.12 (2D), IC10.2 (GND), IC11.2 (GND), IC12.2 (GND), IC13.2 (GND), IC13.6 (C), IC14.2 (GND), IC16.3 (GND), IC18.1 (1A), IC18.2 (1B), IC18.4 (GND), IC19.4 (GND), IC20.10 (GND), IC36.2 (GND), J7.10, J7.23, J7.42, J7.55
M: IC6.9 (2Q), J7.64
Native Latch: IC9.9 (2Q), J7.57
unnamed: IC1.23 (2B7), R3.1
Opcode Valid: IC7.7 (1Y), J7.1
PHI2: IC1.26 (2A7), IC11.1 (1A), J7.39
RDY: IC2.3 (RDY), J7.21, R1.2
R~W: IC1.1 (1DIR), IC2.38 (R~W), IC3.2 (1A0), J7.24, R4.2
VDA: IC2.43 (VDA), IC7.5 (2A), IC8.2 (A), IC16.1 (B), J7.59
VPA: IC2.8 (VPA), IC7.6 (2B), IC8.1 (B), IC16.2 (A), J7.56
VPA·VDA: IC7.2 (1B), IC7.3 (2Y), J7.62
X: IC6.5 (1Q), J7.63
~ABORT: IC1.32 (2A3), J7.44, RN4.6 (R3)
~BANK 0: IC14.4 (Y), J7.33
~IRQ: IC1.30 (2A4), J7.43, RN4.7 (R2)
~ML: IC2.6 (~ML), J7.32
~NMI: IC1.29 (2A5), J7.41, RN4.8 (R1)
~PHI2: IC6.11 (2CP), IC9.3 (1CP), IC11.6 (1Y), J7.25
~RD: IC19.3 (2Y), J7.61
~Reset: IC1.27 (2A6), IC6.4 (~1SD), IC6.10 (~2SD), IC9.13 (~2RD), J7.40
~Trans Output: IC3.15 (~2E), J7.58
~VP: IC2.2 (~VP), J7.31
~WD: IC19.6 (1Y), J7.60
